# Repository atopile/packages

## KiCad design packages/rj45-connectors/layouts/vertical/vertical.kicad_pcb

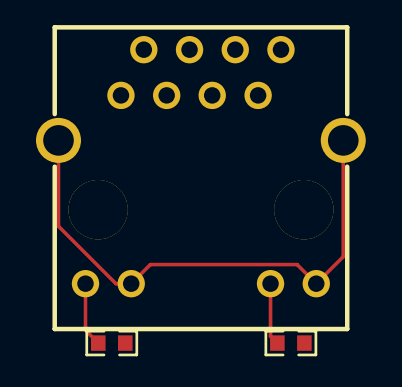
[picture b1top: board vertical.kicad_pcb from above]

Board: 2 copper layers, 3 parts (0 on the bottom side), 3 nets.

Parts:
R1, R2: 10000Ω; R0603
RJ1: RJ45-TH_R-RJ45S08P-C000

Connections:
Gpos: R2.2, RJ1.11
Ypos: R1.2, RJ1.9
lv: RJ1.10, RJ1.12, RJ1.13, RJ1.14

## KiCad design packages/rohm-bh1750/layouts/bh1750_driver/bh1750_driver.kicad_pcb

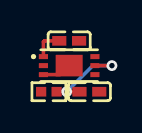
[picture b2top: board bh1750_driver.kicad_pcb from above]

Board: 2 copper layers, 4 parts (0 on the bottom side), 3 nets.

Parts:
C1, C2: 100nF ±10% 16V X7R; C0402
R1: 1kΩ ±1% 62.5mW; R0402
U1: WSOF-6_L2.6-W1.6-P0.50-TL-EP

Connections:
DVI: C2.1, R1.2, U1.5
VCC: C1.1, R1.1, U1.1
gnd: C1.2, C2.2, U1.3, U1.7

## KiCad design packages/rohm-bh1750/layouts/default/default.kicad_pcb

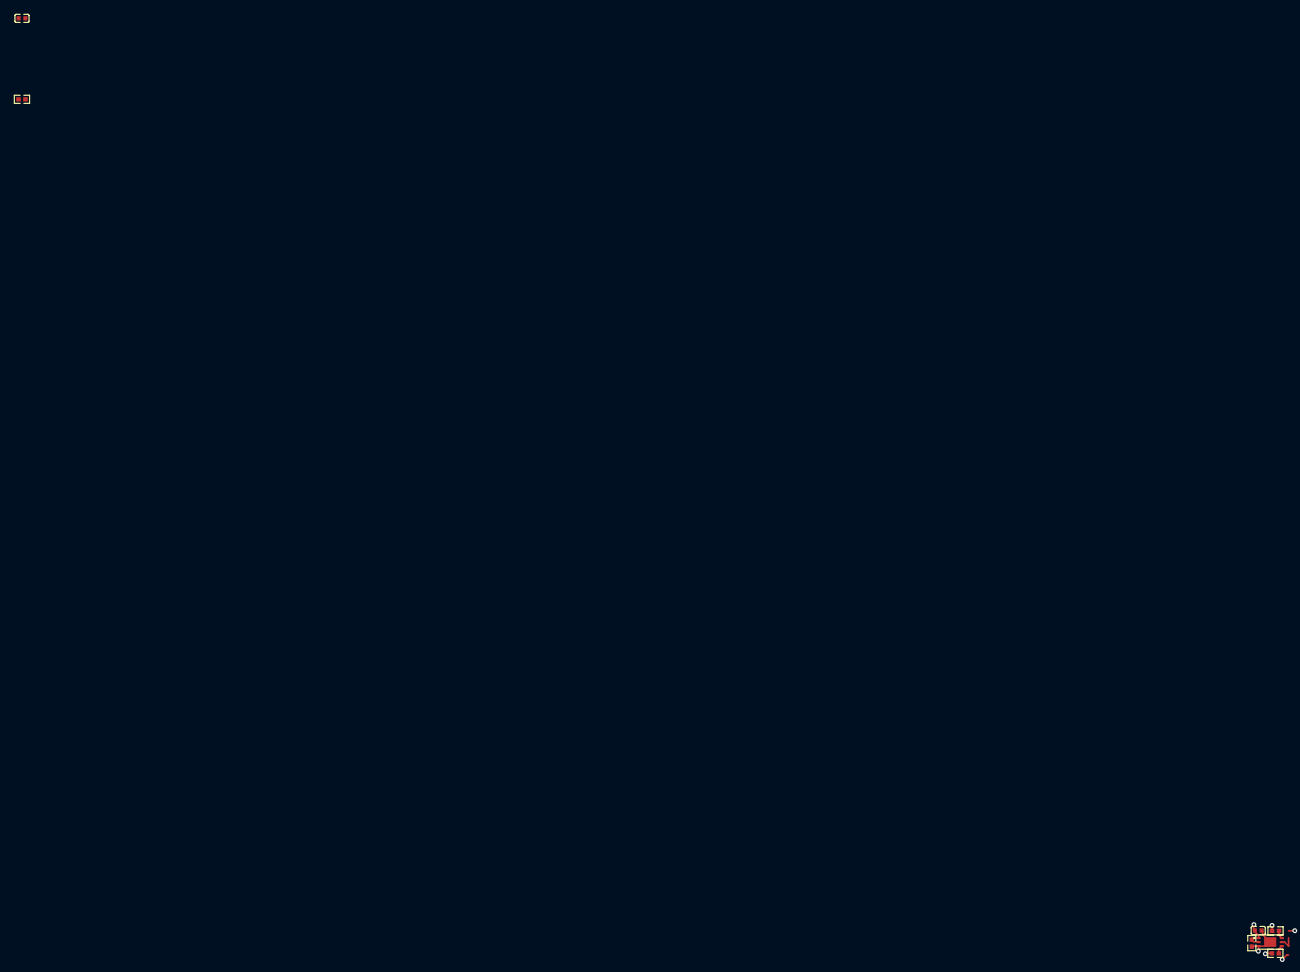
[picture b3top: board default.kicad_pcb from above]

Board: 2 copper layers, 7 parts (0 on the bottom side), 6 nets.

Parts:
C1, C2: 1±10.0%F; C0402
R1: 1000±1.0%Ω; R0402
R2, R3, R4: 10000±1.0%Ω; R0402
U1: WSOF-6_L2.6-W1.6-P0.50-TL-EP

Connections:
ADDR: R2.2, U1.2
SCL: R3.1, U1.6
SDA: R4.1, U1.4
dvi_capacitor-power-hv: C2.1, R1.2, U1.5
hv: C1.1, R1.1, R3.2, R4.2, U1.1
lv: C1.2, C2.2, R2.1, U1.3, U1.7

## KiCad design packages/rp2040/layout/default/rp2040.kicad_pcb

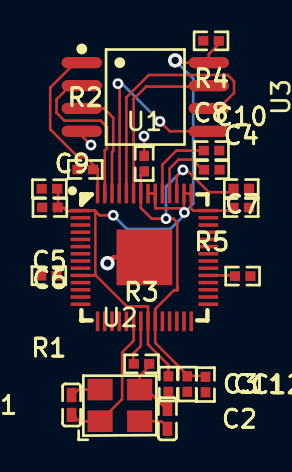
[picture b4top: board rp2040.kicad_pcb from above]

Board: 2 copper layers, 20 parts (0 on the bottom side), 15 nets.

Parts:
C1, C2: 22pF ±5% 50V C0G; C0402-b3ef17
C3, C4, C5, C6, C7, C9, C10, C11: 100nF ±10% 50V X7R; R0402
C8, C12: 1µF ±10% 25V X5R; R0402
R1, R2: 10kΩ ±1% 62.5mW; R0402-56259e
R3: 1kΩ ±1% 62.5mW; R0402-56259e
R4, R5: 27Ω ±1% 62.5mW; R0402-56259e
U1: LQFN-56_L7.0-W7.0-P0.4-EP
U2: OSC-SMD_4P-L3.2-W2.5-BL
U3: SOIC-8_L5.3-W5.3-P1.27-LS8.0-BL

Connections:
cs-1: R2.2, U1.56, U3.1
gnd: C1.2, C2.2, C3.2, C4.2, C5.2, C6.2, C7.2, C8.2, C9.2, C10.2, C11.2, C12.2, U1.19, U1.57, U2.2, U2.4, U3.4
hv: C3.1, C4.1, C5.1, C6.1, C7.1, C8.1, R1.1, R2.1, U1.1, U1.10, U1.22, U1.33, U1.42, U1.43, U1.44, U1.48, U1.49, U3.8
hv-1: C9.1, C10.1, C11.1, C12.1, U1.23, U1.45, U1.50
input: C1.1, U1.20, U2.1
io0: U1.53, U3.5
io1: U1.55, U3.2
io2: U1.54, U3.3
io3: U1.51, U3.7
osc-out: C2.1, R3.2, U2.3
out: R1.2, U1.26
sck-1: U1.52, U3.6
usb_dm: R5.2, U1.46
usb_dp: R4.1, U1.47
xout: R3.1, U1.21

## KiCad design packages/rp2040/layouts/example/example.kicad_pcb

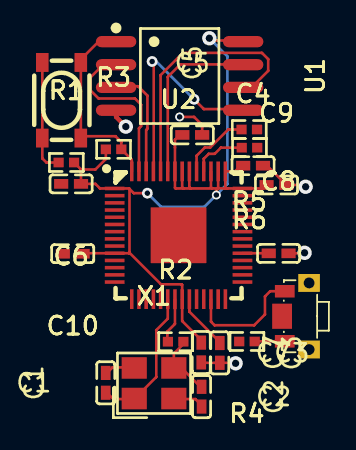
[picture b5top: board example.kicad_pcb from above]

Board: 2 copper layers, 21 parts (0 on the bottom side), 16 nets.

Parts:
C1, C2: 20pF ±5% 50V C0G; C0402
C3, C4, C5, C6, C7, C8, C9, C10: 1µF ±10% 25V X5R; C0402
R1, R3, R4: 10kΩ ±1% 62.5mW; R0402
R2: 1kΩ ±1% 62.5mW; R0402
R5, R6: 27Ω ±1% 62.5mW; R0402
SW1: KEY-SMD_4P-L4.2-W3.2-P2.20-LS4.6
SW2: KEY-SMD_SKTDLDE010
U1: SOIC-8_L5.3-W5.3-P1.27-LS8.0-BL
U2: LQFN-56_L7.0-W7.0-P0.4-EP
X1: CRYSTAL-SMD_4P-L3.2-W2.5-BL

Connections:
OSC2: C2.1, R2.2, X1.3
USB_DM: R6.2, U2.46
USB_DP: R5.2, U2.47
XIN: C1.1, U2.20, X1.1
XOUT: R2.1, U2.21
gnd: C1.2, C2.2, C3.2, C4.2, C5.2, C6.2, C7.2, C8.2, C9.2, C10.2, U1.4, U2.19, U2.57, X1.2, X1.4
hv: C3.1, C4.1, C5.1, C6.1, C7.1, C8.1, C9.1, C10.1, R1.2, R3.1, R4.2, U1.8, U2.1, U2.10, U2.22, U2.23, U2.33, U2.42, U2.43, U2.44, U2.45, U2.48, U2.49, U2.50
input: R1.1, SW1.1, SW1.2
input-1: R4.1, SW2.1
io0: U1.5, U2.53
io1: U1.2, U2.55
io2: U1.3, U2.54
io3: U1.7, U2.51
output: R3.2, SW1.3, SW1.4, U1.1, U2.56
output-1: SW2.2, U2.26
sclk: U1.6, U2.52
